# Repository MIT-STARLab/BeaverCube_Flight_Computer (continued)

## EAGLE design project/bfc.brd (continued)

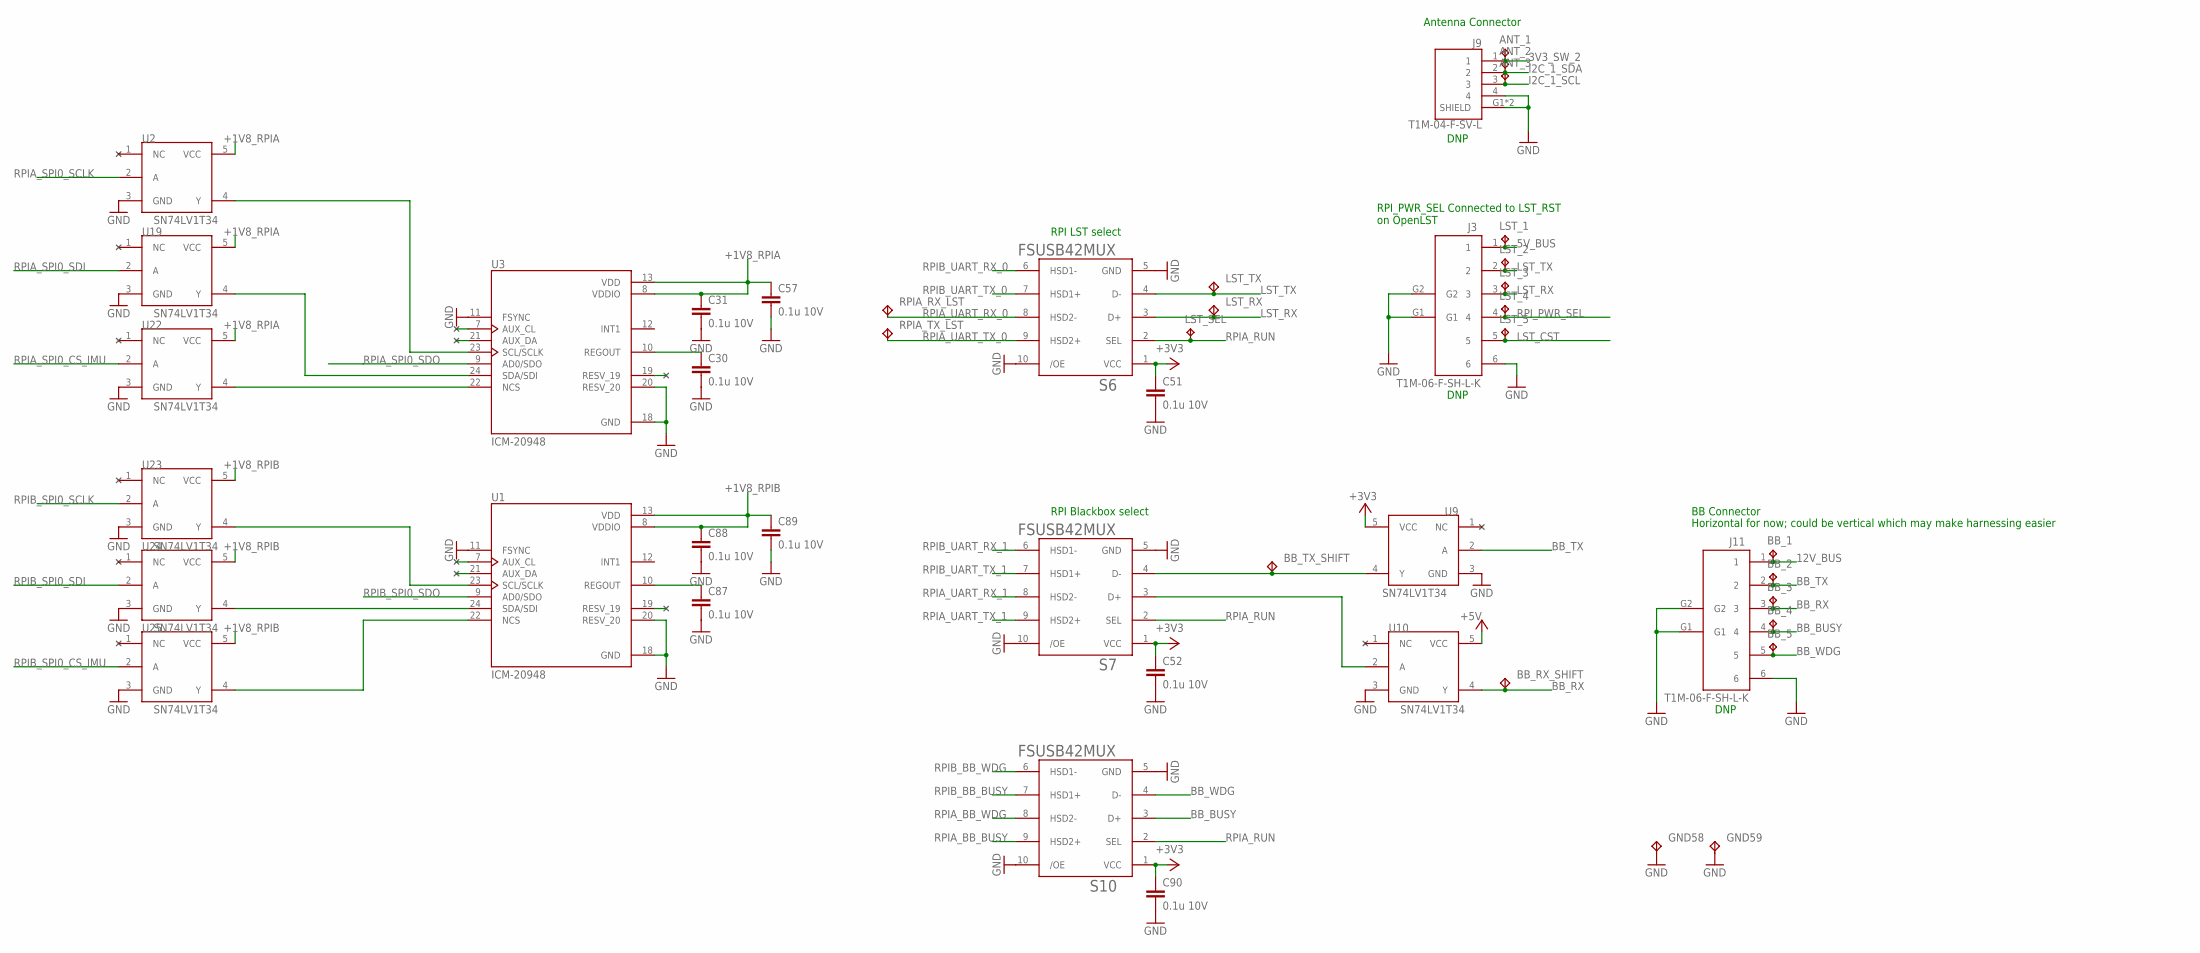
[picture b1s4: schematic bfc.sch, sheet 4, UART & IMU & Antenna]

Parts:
ANT_1, ANT_2, ANT_3: TPTP18SQ; TP18SQ
BB_1, BB_2, BB_3, BB_4, BB_5: TPTP18SQ; TP18SQ
BB_RX_SHIFT: TP_HRWN
BB_TX_SHIFT: TP_HRWN; MPN S2751-46R
C30, C31, C51, C52, C57, C87, C88, C89, C90: 0.1u 10V; C0603
GND58, GND59: TP_HRWN; MPN S2751-46R
J3, J11: T1M-06-F-SH-L-K; MPN T1M-06-F-SH-L
J9: T1M-04-F-SV-L; SAMTEC_T1M-04-F-SV-L; MPN T1M-04-F-SV-L
LST_1, LST_2, LST_3, LST_4, LST_5: TPTP15SQ; TP15SQ
LST_RX: TP_HRWN; MPN S2751-46R
LST_SEL: TPB1,27; B1,27
LST_TX: TP_HRWN; MPN S2751-46R
RPIA_RX_LST: TP_HRWN; MPN S2751-46R
RPIA_TX_LST: TP_HRWN; MPN S2751-46R
S6, S7, S10: FSUSB42MUX; MPN FSUSB42MUX
U1, U3: ICM-20948; QFN40P300X300X105-24N; MPN ICM-20948
U2, U9, U10, U19, U22, U23, U24, U25: SN74LV1T34; SOT23-5; MPN SN74LV1T34DBVR

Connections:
3V3_SW_2: ANT_1.TP, J9.1; also elsewhere on the board
5V_BUS: J3.1, LST_1.TP; also elsewhere on the board
12V_BUS: BB_1.TP, J11.1; also elsewhere on the board
+1V8_RPIA: C31.1, C57.1, U2.5 (VCC), U3.8 (VDDIO), U3.13 (VDD), U19.5 (VCC), U22.5 (VCC); also elsewhere on the board
+1V8_RPIB: C88.1, C89.1, U1.8 (VDDIO), U1.13 (VDD), U23.5 (VCC), U24.5 (VCC), U25.5 (VCC); also elsewhere on the board
+3V3: C51.1, C52.1, C90.1, S6.1 (VCC), S7.1 (VCC), S10.1 (VCC), U9.5 (VCC); also elsewhere on the board
+5V: U10.5 (VCC); also elsewhere on the board
BB_BUSY: BB_4.TP, J11.4, S10.3 (D+)
BB_RX: BB_3.TP, BB_RX_SHIFT.P$1, J11.3, U10.4 (Y)
BB_TX: BB_2.TP, J11.2, U9.2 (A)
BB_WDG: BB_5.TP, J11.5, S10.4 (D-)
GND: C30.2, C31.2, C51.2, C52.2, C57.2, C87.2, C88.2, C89.2, C90.2, GND58.P$1, GND59.P$1, J3.6, J3.G1, J3.G2, J9.4, J9.G1 (SHIELD), J9.G2 (SHIELD), J11.6, J11.G1, J11.G2, S6.5 (GND), S6.10 (/OE), S7.5 (GND), S7.10 (/OE), S10.5 (GND), S10.10 (/OE), U1.11 (FSYNC), U1.18 (GND), U1.20 (RESV_20), U2.3 (GND), U3.11 (FSYNC), U3.18 (GND), U3.20 (RESV_20), U9.3 (GND), U10.3 (GND), U19.3 (GND), U22.3 (GND), U23.3 (GND), U24.3 (GND), U25.3 (GND); also elsewhere on the board
I2C_1_SCL: ANT_3.TP, J9.3; also elsewhere on the board
I2C_1_SDA: ANT_2.TP, J9.2; also elsewhere on the board
LST_CST: J3.5, LST_5.TP
LST_RX: J3.3, LST_3.TP, LST_RX.P$1, S6.3 (D+)
LST_TX: J3.2, LST_2.TP, LST_TX.P$1, S6.4 (D-)
unnamed: C87.1, U1.10 (REGOUT)
unnamed: U2.4 (Y), U3.23 (SCL/SCLK)
unnamed: U3.24 (SDA/SDI), U19.4 (Y)
unnamed: U3.22 (NCS), U22.4 (Y)
unnamed: U1.23 (SCL/SCLK), U23.4 (Y)
unnamed: U1.22 (NCS), U25.4 (Y)
unnamed: U1.24 (SDA/SDI), U24.4 (Y)
unnamed: C30.1, U3.10 (REGOUT)
unnamed: BB_TX_SHIFT.P$1, S7.4 (D-), U9.4 (Y)
unnamed: S7.3 (D+), U10.2 (A)
RPIA_BB_BUSY: S10.9 (HSD2+); also elsewhere on the board
RPIA_BB_WDG: S10.8 (HSD2-); also elsewhere on the board
RPIA_RUN: LST_SEL.TP, S6.2 (SEL), S7.2 (SEL), S10.2 (SEL); also elsewhere on the board
RPIA_SPI0_CS_IMU: U22.2 (A); also elsewhere on the board
RPIA_SPI0_SCLK: U2.2 (A); also elsewhere on the board
RPIA_SPI0_SDI: U19.2 (A); also elsewhere on the board
RPIA_SPI0_SDO: U3.9 (AD0/SDO); also elsewhere on the board
RPIA_UART_RX_0: RPIA_RX_LST.P$1, S6.8 (HSD2-); also elsewhere on the board
RPIA_UART_RX_1: S7.8 (HSD2-); also elsewhere on the board
RPIA_UART_TX_0: RPIA_TX_LST.P$1, S6.9 (HSD2+); also elsewhere on the board
RPIA_UART_TX_1: S7.9 (HSD2+); also elsewhere on the board
RPIB_BB_BUSY: S10.7 (HSD1+); also elsewhere on the board
RPIB_BB_WDG: S10.6 (HSD1-); also elsewhere on the board
RPIB_SPI0_CS_IMU: U25.2 (A); also elsewhere on the board
RPIB_SPI0_SCLK: U23.2 (A); also elsewhere on the board
RPIB_SPI0_SDI: U24.2 (A); also elsewhere on the board
RPIB_SPI0_SDO: U1.9 (AD0/SDO); also elsewhere on the board
RPIB_UART_RX_0: S6.6 (HSD1-); also elsewhere on the board
RPIB_UART_RX_1: S7.6 (HSD1-); also elsewhere on the board
RPIB_UART_TX_0: S6.7 (HSD1+); also elsewhere on the board
RPIB_UART_TX_1: S7.7 (HSD1+); also elsewhere on the board
RPI_PWR_SEL: J3.4, LST_4.TP; also elsewhere on the board

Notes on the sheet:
RPI LST select
RPI Blackbox select
RPI_PWR_SEL Connected to LST_RST on OpenLST
Antenna Connector
BB Connector
Horizontal for now; could be vertical which may make harnessing easier
DNP

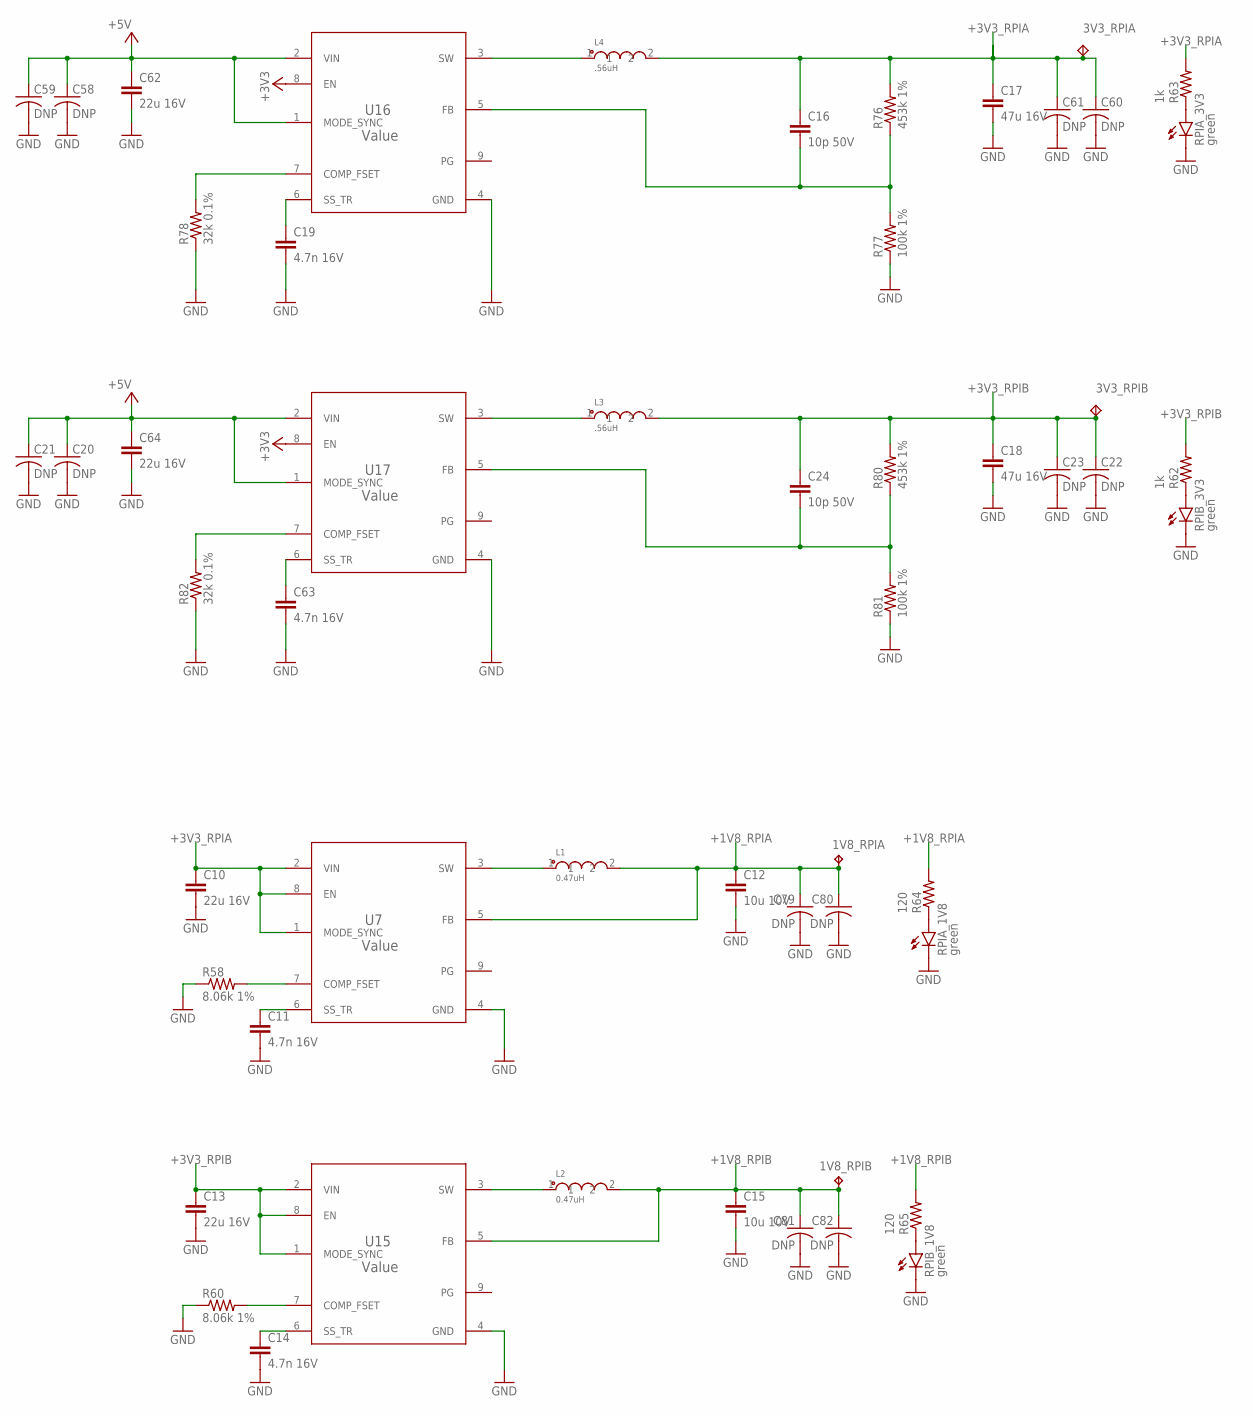
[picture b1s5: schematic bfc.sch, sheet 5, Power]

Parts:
1V8_RPIA, 1V8_RPIB: TPB1,27; B1,27
3V3_RPIA, 3V3_RPIB: TP_HRWN; MPN S2751-46R
C10, C13, C62, C64: 22u 16V; C1206
C11, C14, C19, C63: 4.7n 16V; C0603
C12, C15: 10u 10V; C1206
C16, C24: 10p 50V; C0603
C17, C18: 47u 16V; C1210
C20, C21, C22, C23, C58, C59, C60, C61, C79, C80, C81, C82: DNP; C0805
L1, L2: 0.47uH; LPS3010; MPN LPS3010-471MRC
L3, L4: .56uH; INDP_LPS4018-472MRB; MPN LPS4018-561MRC
R58, R60: 8.06k 1%; R0603
R62, R63: 1k; R0603
R64, R65: 120; R0603
R76, R80: 453k 1%; R0603
R77, R81: 100k 1%; R0603
R78, R82: 32k 0.1%; R0603
RPIA_1V8: green; SML0603; MPN LG L29K-F2J1-24-Z
RPIA_3V3: green; SML0603; MPN 150060VS75000
RPIB_1V8: green; SML0603; MPN LG L29K-F2J1-24-Z
RPIB_3V3: green; SML0603; MPN 150060VS75000
U7, U15: Value; RWY0009A; MPN TPS628112MQWRWYRQ1
U16, U17: Value; RWY0009A; MPN TPS62812QWRWYRQ1

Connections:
1: C24.2, R80.1, R81.2, U17.5 (FB)
2: C16.2, R76.1, R77.2, U16.5 (FB)
3: L3.1, U17.3 (SW)
7: L4.1, U16.3 (SW)
+1V8_RPIA: 1V8_RPIA.TP, C12.1, C79.1, C80.1, L1.2, R64.2, U7.5 (FB); also elsewhere on the board
+1V8_RPIB: 1V8_RPIB.TP, C15.1, C81.1, C82.1, L2.2, R65.2, U15.5 (FB); also elsewhere on the board
+3V3: U16.8 (EN), U17.8 (EN); also elsewhere on the board
+3V3_RPIA: 3V3_RPIA.P$1, C10.1, C16.1, C17.1, C60.1, C61.1, L4.2, R63.2, R76.2, U7.1 (MODE_SYNC), U7.2 (VIN), U7.8 (EN); also elsewhere on the board
+3V3_RPIB: 3V3_RPIB.P$1, C13.1, C18.1, C22.1, C23.1, C24.1, L3.2, R62.2, R80.2, U15.1 (MODE_SYNC), U15.2 (VIN), U15.8 (EN); also elsewhere on the board
+5V: C20.1, C21.1, C58.1, C59.1, C62.1, C64.1, U16.1 (MODE_SYNC), U16.2 (VIN), U17.1 (MODE_SYNC), U17.2 (VIN); also elsewhere on the board
GND: C10.2, C11.2, C12.2, C13.2, C14.2, C15.2, C17.2, C18.2, C19.2, C20.2, C21.2, C22.2, C23.2, C58.2, C59.2, C60.2, C61.2, C62.2, C63.2, C64.2, C79.2, C80.2, C81.2, C82.2, R58.1, R60.1, R77.1, R78.1, R81.1, R82.1, RPIA_1V8.C, RPIA_3V3.C, RPIB_1V8.C, RPIB_3V3.C, U7.4 (GND), U15.4 (GND), U16.4 (GND), U17.4 (GND); also elsewhere on the board
unnamed: R78.2, U16.7 (COMP_FSET)
unnamed: C19.1, U16.6 (SS_TR)
unnamed: R82.2, U17.7 (COMP_FSET)
unnamed: C63.1, U17.6 (SS_TR)
unnamed: C11.1, U7.6 (SS_TR)
unnamed: R58.2, U7.7 (COMP_FSET)
unnamed: L1.1, U7.3 (SW)
unnamed: R60.2, U15.7 (COMP_FSET)
unnamed: C14.1, U15.6 (SS_TR)
unnamed: L2.1, U15.3 (SW)
unnamed: R62.1, RPIB_3V3.A
unnamed: R63.1, RPIA_3V3.A
unnamed: R64.1, RPIA_1V8.A
unnamed: R65.1, RPIB_1V8.A

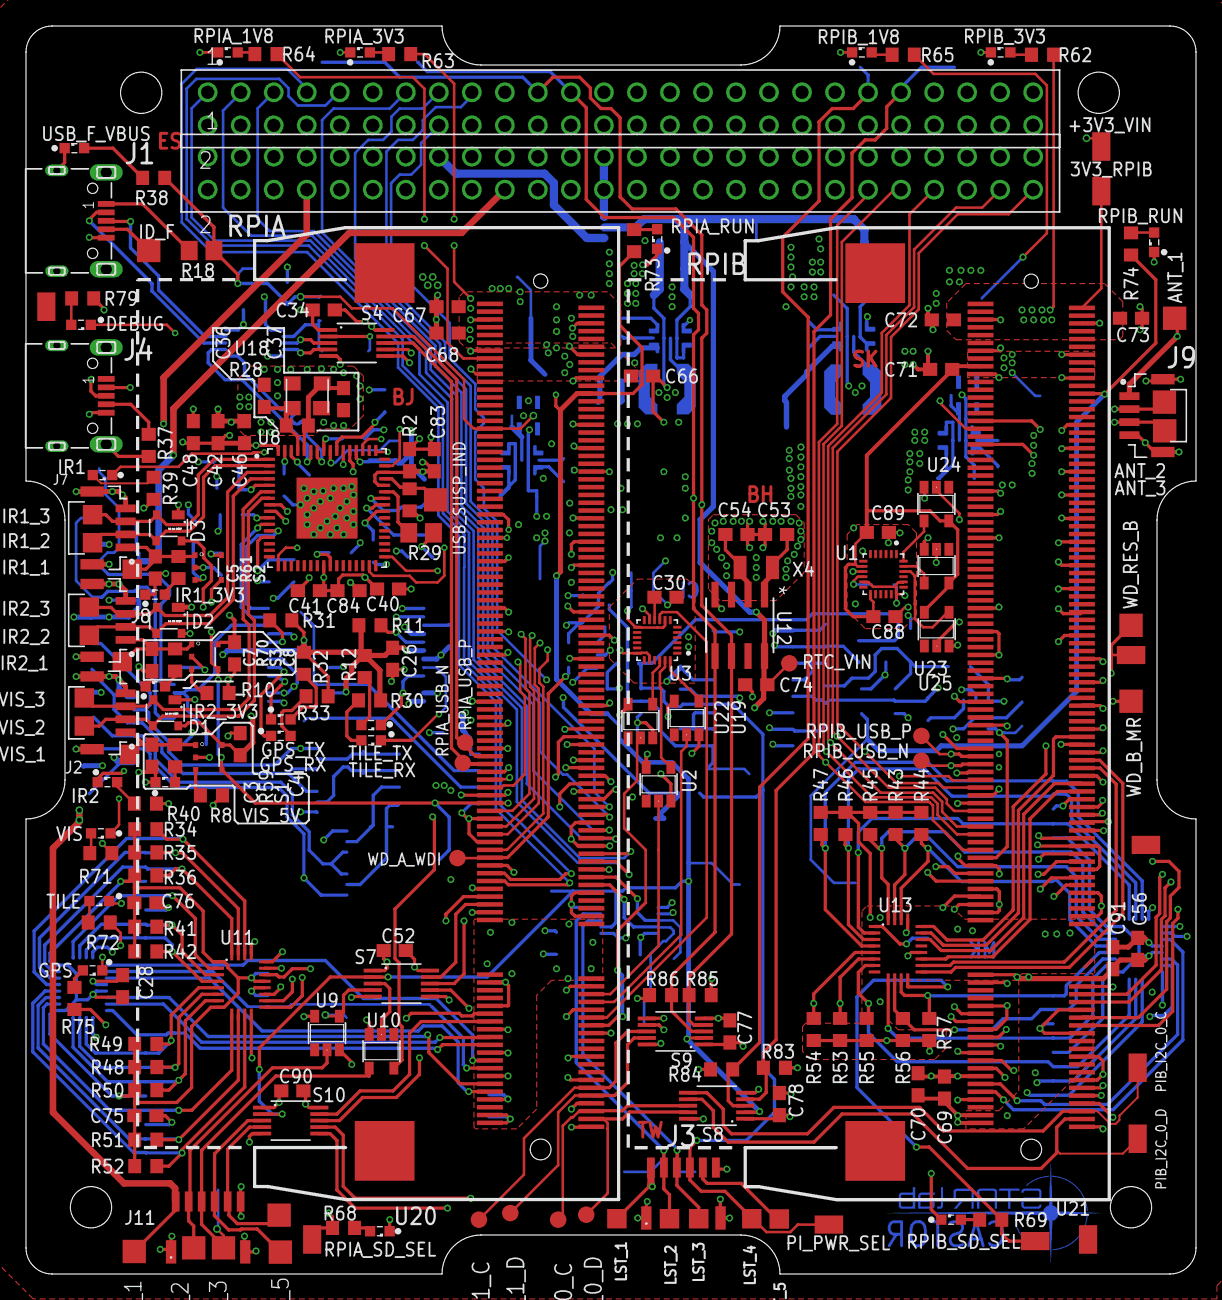
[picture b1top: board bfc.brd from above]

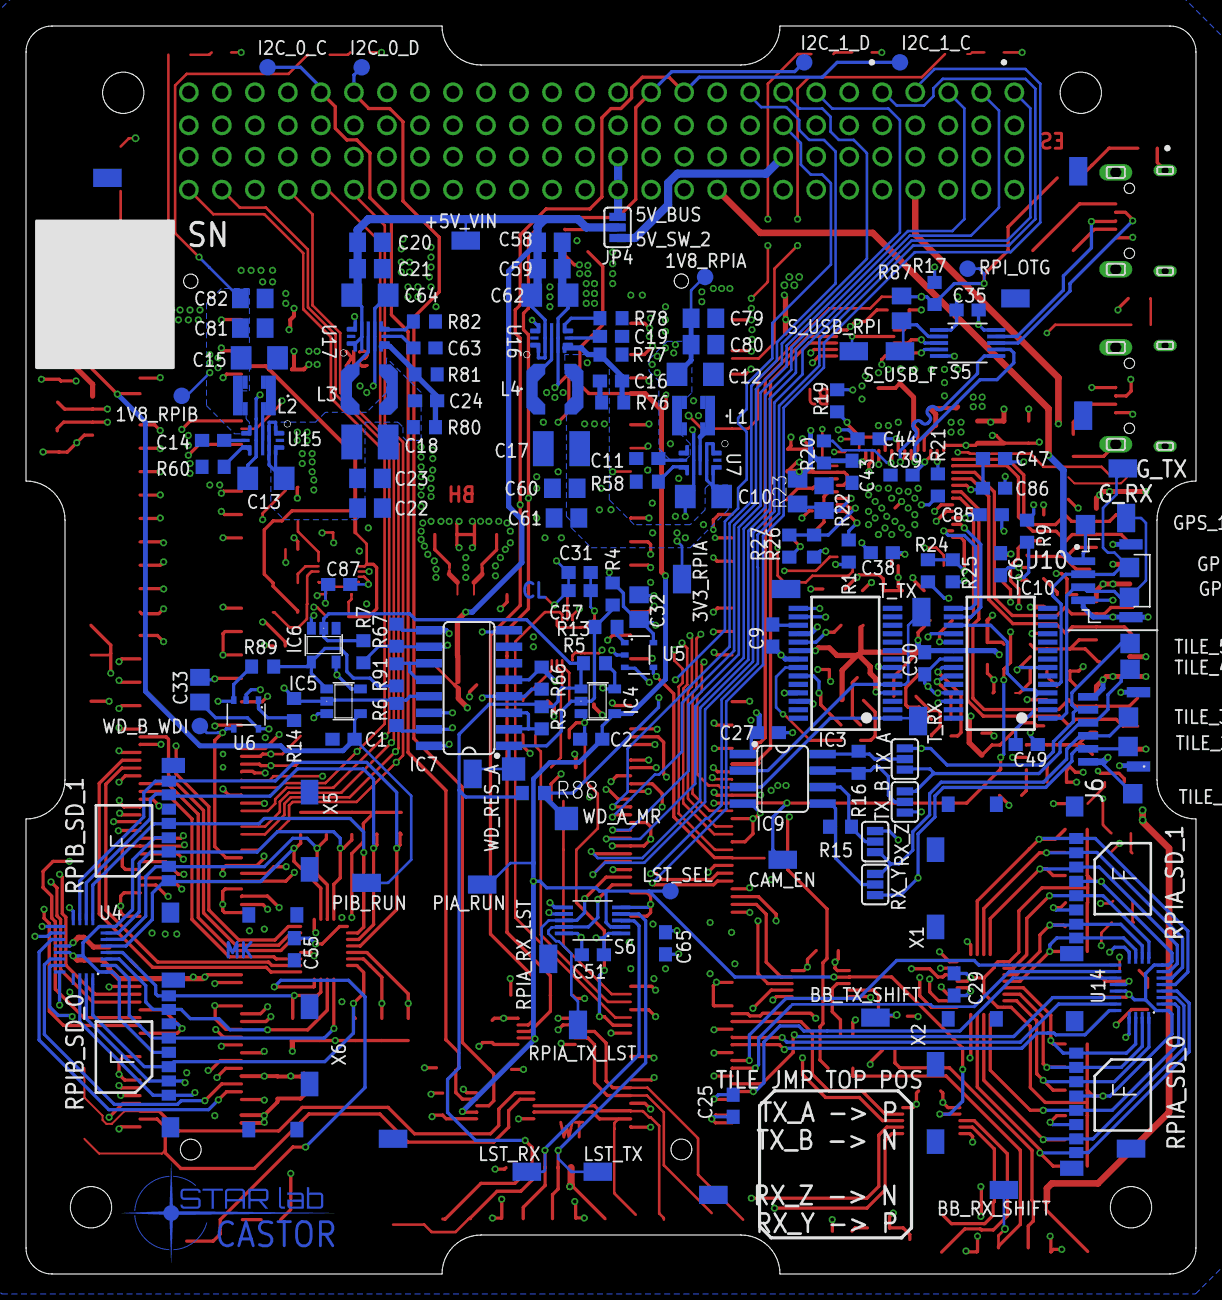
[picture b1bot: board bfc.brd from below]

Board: 6 copper layers, 90.0 x 96.0 mm, 366 parts (163 on the bottom side), 251 nets.

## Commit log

2020-05-15 Create test
2020-05-15 Added schematic and board from most recent build
    Only change from most recent build is the MPN for the JK flip flop, since part number did not match footprint
2020-05-15 added eagle library files
2020-05-15 adding .gitignore
2020-05-15 modified gitignore to NOT ignore all files
2020-05-15 fixed 1 DRC error. Trace dragged over pad accidentally during previous brd viewing
2020-07-02 adding known errors
2020-07-02 Added all known issues in testing as of 7.01
2020-07-02 removed protected graphics on bottom of board
